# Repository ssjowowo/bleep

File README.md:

# Bleep

**A DIY touchscreen universal remote.** It's built around an ESP32-S3 on a main board of our own, with a 3.5″ IPS touch display, 14 physical keys, IR send and learn, haptics, and Home Assistant control over Wi-Fi. The case is 3D-printed and only 13 mm thick.

<p align="center">
  
  &nbsp;
  
</p>

## What it is

Most universal remotes either have a screen and few buttons, or lots of buttons and no screen. Bleep has both. The touchscreen shows activities, now-playing and smart-home controls. The keys you use without looking stay physical: a D-pad ring with OK, Back, Home, Mute, three app keys (YouTube, Netflix, Plex) and a volume rocker.

- **IR out**: two side-view 940 nm IR LEDs at the top end control TVs, receivers and boxes.
- **IR learning**: a 38 kHz receiver behind a small window under the screen copies codes from your old remotes.
- **Wi-Fi**: Home Assistant control of lights, scenes and media through the ESP32-S3.
- **Feel**: a coin vibration motor driven by a DRV2605L haptics driver.
- **Smart power**: lift-to-wake (accelerometer), wake on touch or any key, auto-brightness (light sensor), and a fuel gauge for an accurate battery percentage. Asleep it draws about 0.1–0.15 mA, so a charge lasts months.
- **USB-C** for charging and flashing.

The hardware is designed for all of this. The firmware's app and UI run today in an emulator (on the PC or in a browser) while the boards are being made; the ESP32-S3 port comes when they arrive. See [firmware/README.md](firmware/README.md).

The industrial design comes from a concept pack made in Claude Design (design **1b "Pebble"**, in `design/`). The brand (wordmark, logo lockup) comes from the Bleep brand book.

## Status

| Part | State |
|---|---|
| Main board v1 | **Ordered** from JLCPCB on 2026-10-08 (5 boards, 2 assembled). The design is locked: the files in `hardware/mainboard/` are the ones in production. |
| Enclosure | Ready to print. 15.0 mm thick since 2026-11-13: the cell lies on the flat, uniform 1.5 mm back plate, which drops in and slides home under ledges in the side walls; back edges rounded 3 mm. |
| Display | BuyDisplay ER-TFT035IPS-6 + capacitive touch, **ordered** 2026-10-09. Its cable fold gets checked on the real panel before assembly. |
| Battery | EEMB 524261, 1500 mAh (sold as 5.2 mm, measured 5.5–6.0 mm thick); `BATT` in `layout.py` is set for 6.0 mm. |
| Firmware | App and UI (C + LVGL 9) running in a PC/browser emulator with 53 scripted test scenarios; the ESP-IDF build runs on the first board (since 2026-11-02), with a Home Assistant client tested against a real Home Assistant. [firmware/](firmware/) |

## Hardware at a glance

| | |
|---|---|
| Size | 60.7 × 182.2 × 15.0 mm |
| MCU | ESP32-S3-WROOM-1-N8R2 (8 MB flash, 2 MB PSRAM), antenna at the right edge beside the D-pad |
| Display | 3.5″ IPS 320 × 480, ILI9488 on an 8-bit parallel bus (much faster than SPI), FT6236 capacitive touch |
| Keys | 14 tactile switches, each on its own wake-capable GPIO |
| IR | 2 × VSMB2948SL LEDs (≈ 125 mA peaks), IRM-H638T receiver for learning |
| Sensors | MMA8452Q accelerometer, LTR-303ALS light sensor, MAX17048 fuel gauge |
| Power | 1-cell Li-Po, TP4056 charger with load sharing, ME6211 3.3 V LDO |
| Board | 2 layers, 0.8 mm, 54 × 178 mm. JLCPCB assembles the top side; you solder the ESP32 module, battery and motor on the underside. |
| Case | PETG, two colours for the key labels (flush inlays), plus translucent blue PETG for the IR and sensor windows (two small separate prints); the board screwed to the front shell (4 × M2×4) and the back plate dropped in and slid home under side ledges and two top hooks, then held by 2 × M2×10, all into heat-set inserts |

The parts list, pin map, assembly steps, ordering guide (≈ €130 in total, delivered to Cyprus) and firmware notes are in **[hardware/README.md](hardware/README.md)**.

## How it's built

Everything mechanical comes from one file, [`hardware/layout.py`](hardware/layout.py). It holds the display and part sizes, the key layout, where each part sits, the z stack and the screw points, and it runs fit checks on all of them. Two generators read it:

- **Enclosure**: `layout.py` writes `enclosure/params.scad`, and [`enclosure/remote.scad`](hardware/enclosure/remote.scad) (OpenSCAD) builds the front shell, its two windows, back plate, key caps and label inlays as STLs, plus interference checks.
- **Main board**: [`mainboard/gen_mainboard.py`](hardware/mainboard/gen_mainboard.py) places the parts in KiCad 10 from the same numbers. [Freerouting](https://github.com/freerouting/freerouting) routes it, then the generator adds ground pours, runs DRC and exports Gerbers, BOM and CPL for JLCPCB.

The board and the case can't drift apart. Since the board was ordered, `layout.py` checks every value the board was built from against `mainboard/pcb_lock.json`. It refuses to run if a case change would move one of them.

## Repository layout

```
design/              concept pack (open the .dc.html files in a browser), brand assets, outline drawings
hardware/
  layout.py          the single source of truth for the mechanics
  build.sh           rebuilds everything from layout.py
  enclosure/         OpenSCAD source and the printable STLs (enclosure/stl/)
  mainboard/         KiCad board, generator, routing logs; fab/ = Gerbers, BOM, CPL (locked)
  viewer/            3D colour viewer (three.js) for trying colourways
  docs/              datasheets and renders
HANDOFF.md           current working state, for picking the project up on another machine
```

## Building

```bash
cd hardware
./build.sh enclosure   # STLs, renders and fit checks
./build.sh viewer      # meshes for the 3D viewer (viewer/index.html)
```

You need Python 3 (no extra packages) and OpenSCAD 2021.01 or newer, on the PATH or set with `OPENSCAD=`. The board rebuild (`./build.sh pcb`) also needs KiCad 10 and Freerouting, and it's disabled while v1 is locked.

To open the 3D viewer locally, run `python3 -m http.server -d hardware/viewer 8742` and go to <http://localhost:8742>.

## Roadmap

1. Boards and display arrive: check the display cable fold, solder the underside parts, print the case.
2. Firmware: LVGL UI (activities, now playing, Home Assistant), IR send and learning through the RMT peripheral, deep sleep with key, touch and lift wake.
3. Fixes found on the real hardware go into a v2 board.

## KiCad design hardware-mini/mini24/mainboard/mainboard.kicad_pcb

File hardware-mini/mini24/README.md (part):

# Bleep mini24 — hardware (2.4" panel)

A hand-built Bleep with a 2.4" 240 × 320 IPS touch panel: v1's design language (glass to the top end, 5/20 mm corners, IR window in the top wall, sensor window + power key in the row under the screen, ring D-pad + OK, round keys, app pills, split volume bar, USB-C at the bottom), a smaller shell, a replaceable 1500 mAh cell on a connector (under the keys, for the balance in the hand), a PDM microphone and a 32 kHz crystal. Built in small quantities: JLCPCB makes the board and places the top side (Economic PCBA); the underside parts (the ESP32 module, the battery connector with its protection FET and resistor, the motor's wires) are soldered by hand with an iron; the rest comes from LCSC, AliExpress and Ampul.

| | |
|---|---|
| Shell | **46.92 × 159.51 × 15.73 mm** |
| Display | BuyDisplay ER-TFT024IPS-3 (ST7789V, 4-wire SPI) + ER-TPC024-1 touch (FT6336U, I²C), one 50-pin FPC, 4.23 mm |
| ESP32 | ESP32-S3-WROOM-1-**N8R2** (PCB antenna), across the board on the underside, antenna at the right edge |
| Cell | **Ampul AM4289 "504050"**, 5.0 × 40 × 50 mm, 1500 mAh, PCM, on a Molex PicoBlade plug; **under the keys** (y 91.5–141.5), behind a printed deck |
| Main board | 40.12 × 154.8 mm (incl. the USB tab), 2 layers, 0.8 mm, **green mask, lead-free HASL** (what JLC's Economic PCBA allows at 0.8 mm); a 13.65 × 9.55 mm window under the panel FPC's touch section |
| Assembly | **JLCPCB Economic PCBA, top side only**; you solder the underside by iron: U1 (module), J2 (PicoBlade) with Q4 (SOT-23) and R28 (0603) beside it, the motor's wires, J3's four shell legs, and the module's EPAD through its three holes (§6) |

Everything comes from [`layout.py`](layout.py) (the mechanical source of truth: positions, stack, GPIO map, fit checks):

```bash
./build.sh            # fit checks, STLs + interference checks, board (place/route/DRC/fab), viewer meshes
./build.sh enclosure  # params.scad, STLs, interference + insertion-path checks
./build.sh pcb        # main board: place -> Freerouting -> SES -> pours/refs/BOM -> DRC -> fab outputs
./build.sh viewer     # ../viewer/mini24.json
```

Needs Python 3, OpenSCAD (`~/.local/bin/openscad`), and Docker with `../tools/kicad.sh` (KiCad 10) and `../tools/freerouting.sh` (Freerouting 2.5). Set `BLEEP_LOCK=/path/heavy.lock` to serialise the heavy steps with another build.

**Status (2026-10-13, cell moved under the keys, §14):** fit checks pass; OpenSCAD interference checks empty / zero volume, insertion-path checks empty; board fully routed, KiCad DRC (all severities) **0 violations / 0 unconnected**; Gerbers, drill, BOM, position file, assembly drawings and renders in `mainboard/fab/`. Not built yet. The mini28 audit's findings that apply here are built in (§9), and so are the mini24 audit's (§10) and the final audit's (§11).

---

## 1. The antenna problem and how it's solved

The WROOM-1's keep-out (no copper on either layer from 1.5 mm before the antenna section to the board edge, 3.5 mm past the module's long sides) is a 7.8 × 25 mm block at the right edge. On this 40 mm board v1's layout would have put the D-pad's RIGHT switch and the right-column power key inside it (that's why the concept failed v1's checks).

**Chosen:** keep the module across the board on the underside with its antenna 0.3 mm inside the right edge (the best spot for a PCB antenna short of overhanging the board), put it **directly below the folded display FPC**, and start the key cluster **below the keep-out**:

- The keep-out begins 0.3 mm below the fold's outer edge (y 67.66) and ends at y 92.96 (the board's rule area). The D-pad's RIGHT switch body (+1 mm) starts right after it. The UP switch and the power key sit over the module (on the top side), which is fine: only copper within the keep-out matters, and the module carries them.
- The **power key moves 4.5 mm in from the right column** (x 31.5 instead of 35.96), so its pads stay 0.7 mm clear of the keep-out. The row under the screen reads: sensor window (left column), mic hole (centre), power key (right of centre).
- Posts and screws are ≥ 4 mm from the keep-out (since §14 there is no screw on the right between the screen and the bottom boss; the nearest is H1, at the far left).
- Cost: about 1 mm of length over the concept (159.5 vs 158.2 mm; the last 0.3 is the IR LEDs' clearance to a panel slid up in its pocket), partly paid back by tightening the key rows (row pitch 23.0/11.5/10.0 instead of 23.5/12/10) and by a realistic, shorter FPC fold.

**Rejected:**
- Module lengthwise or at the bottom: the antenna end would sit in the 20 mm bottom corner, where the board is narrower than the keep-out; +20 mm of length.
- D-pad off-centre (2.3 mm left): breaks the design language.
- **WROOM-1U + U.FL FPC antenna** ([C3013944](https://www.lcsc.com/product-detail/C3013944.html) + Molex 146153-0050): there's no place for a 35 × 9 mm antenna that's away from the cell, the panel and the board's ground (the side walls are 1.6 mm from the board edge; under the key area it would sit 5 mm under a ground pour); 133 antennas in stock. Kept as the fallback.

Expect the antenna to be somewhat detuned by the hand and the PETG wall (1.6 mm away; Espressif asks for much more). Measure RSSI against v1 on the first build.

---

## 2. Stack (z from the back face, 5.0 mm cell)

| z (mm) | |
|---|---|
| 0 – 1.5 | back plate (flat, removable: 2 screws into the deck + 2 snap fingers) |
| 1.5 – 6.5 | **under the keys: the cell** (y 91.5–141.5) on the plate between its two side rails, +0.5 swell gap to 7.0. Under the screen and the module (open down to the plate): the module (3.1), the battery connector + plug (3.4) and Q4/R28 left of the module, the motor (3.3) under the screen, the plate's pillars and LCD fins, H1's head (1.6) |
| 7.0 – 7.6 | **the deck** (printed, 0.6 mm) under the key area, from y 90.26 down; the two bottom board screws' heads hang under it |
| 7.6 – 8.4 | main board, 0.8 mm (with a window under the touch section, see below) |
| 8.4 – 10.7 | under the LCD: **2.3 mm** — the panel FPC with the touch section, J1 (1.0), foam pads (1.5 + 1.0 mm soft foam, 8 % compressed) |
| 10.7 – 13.0 | LCD (2.3) |
| 13.0 – 14.93 | touch panel (PET on glass, 1.93) |
| 14.93 – 15.73 | front frame over the glass (0.8) |

Key area: front wall inner face z 14.13, switch actuators z 9.90, stems 3.53 mm with 0.1 mm designed play. The cell's thickness and the deck drive H (15.13 + the 0.6 mm deck): a 6 mm cell (604050, 1600 mAh, or 603450) would make it 16.73 mm, over the 16 mm limit (`layout.py` reports it).

**The touch section and the 2.3 mm gap (mini24 audit M1).** The panel's 50-pin FPC carries the touch panel's own tail soldered onto its contact face: the FT6336U and its parts on a 9 × 11 mm, 0.2 mm steel stiffener, rigid, up to 1.7 mm tall incl. the FPC. Along the FPC (DS 3.3 front and side views, the ER-TPC024-1 drawing, the listing photo) it sits at **s ≈ 12.5–21.5 mm** from the BL edge; its tall part ends at s ≈ 17–19. **Across**, it is placed by the ER-TPC024-1 drawing's own dimensions (final audit M1), measured from the lens's left edge (shell x 2.1): the CTP tail's 6-pad solder strip starts **9.61** in and is **4.00** wide (x 11.71–15.71, thin), and the **11.00 × 9.00** steel-stiffened controller box lies right of it: **x 15.71–26.71**, with the FT6336U at ≈ x 18.6–23.9 (scaled, the only undimensioned part). DS 3.3's front view agrees within 0.2 mm. That leaves only ≈ 0.5 mm of flexible FPC before the main tail's own stiffener (s 22–27), which must lie flat in J1 at the board. After the fold, the parts face the board.
- A taller bottom-contact ZIF (the audit's option a) doesn't solve it: its contact slot stays at the board (only its lid grows, per the PH15/PH20 drawings), so the FPC still has to come down to ≈ 0.3 mm above the board. J1 stays the 1.0 mm FH34SRJ.
- Instead the gap under the LCD grows from 2.0 to **2.3 mm** (shell +0.3 mm) and the board gets a **window** (**x 14.40–28.05, y 48.90–58.45**, 13.65 × 9.55 mm, 0.5 mm corner radii) under the controller box: the box ± 0.8 mm, plus ± 0.5 mm for the tail's lateral position, and its tall part's s range ± 1 mm. No copper within 0.45 mm of the cut. The section lies **tilted ≈ 10°**: its J1 end just above J1's slot (the 0.5 mm flex only bends gently, no S; its thin steel end may rest on the board's solder mask), its fold end just under the LCD's back, its tall part dipping into the window — at most to the board's underside, never below it (since §14 only open space and the back plate are behind it). The window stops 3.3 mm short of J1 so the display signals still have a way round to J1's pads. The window's coordinates are written as numbers in `layout.py`, not derived from the section, and `check()` tests them against the drawing-derived box (+0.8 +0.5 each side) and the tall part's s range (±1), so the check can't pass by construction; `remote.scad`'s FPC model places the strip and the box from the same drawing constants, and `fpc_vs_parts` sees them.
- **If the parts face the other way** (up), the section lies flat at J1's height with its parts in the 2.3 mm gap, 0.3 mm under the LCD: that also passes the checks, so the design doesn't depend on the facing.
- The 1:1 mock-up with the real panel (§6 step 0) settles s, the facing and the heights **before the boards are ordered**.

---

## 3. The cell, and why

**Ampul AM4289 "504050": 5.0 × 40 × 50 mm, 1500 mAh, 5.55 Wh, protection circuit fitted, bare leads** (€8.13, "in stock at supplier"; [ampul.eu](https://ampul.eu/en/battery/4395-li-pol-battery-1500mah-37v-504050)).

- DESIGN.md's first choice. **Where it sits (since 2026-10-13, §14): under the keys**, on the back plate right below the module (the module can't go under the panel: the LCD's metal frame would detune its antenna). The bay runs from 0.6 mm below the module's pocket (y 90.66) to y 142.36: **51.70 mm stop to stop, 41.22 mm between the plate's two side rails** (0.8 mm wide, rising beside the cell in the board-to-wall gap, down to the bottom stops' line; 0.61 mm clear per side of a 40 mm cell). Small chamfered stops (2 mm wide, 1.5 mm tall) hold its ends: at the top (lead) end 8 mm either side of the centre, away from the corners where the leads leave, under the module; at the bottom end 3.5 mm either side of the centre.
- **The bay takes cells up to 40.0 × 50.5 mm** including the PCM (0.6 mm to spare per side and at each end; `layout.py` prints the same). Margins of the nominal cell (y 91.51–141.51): **2.05 mm to the module's outline** (1.45 to its pocket), for a centred cell **0.69 mm** from its bottom corners to where the plate's lip would be; the lip is cut away beside the bottom corners, so even a cell pushed into a corner (against a rail and a stop) keeps **0.81 mm to the wall** and touches only the rail and the stop; **1.5 mm** to the deck's bosses, **7.0 mm** to the bottom board screws' heads, **8.5 mm** to the zone kept for the USB-C's underside joints. ≤ 5.0 mm thick.
- **The deck** (§14) lies 0.5 mm over the cell (its swell gap) and carries the keys, so a key press doesn't land on the cell.
- Compared: 603560 (6 × 35 × 60, 1500 mAh) is 1 mm thicker for the same capacity and 10 mm longer: it doesn't fit under the keys; 604050 (1600 mAh) is +7 % for +1 mm: the shell would be 16.73 mm, over the 16 mm limit now that the deck is in the stack. Fallback 603450 (1200 mAh, 6 mm) likewise doesn't fit the limit any more.
- Charge current 500 mA (PROG 2.4 k, 0.33 C).
- Runtime ≈ 3.3 weeks at 15 min/day (scaled from v1's estimate; unverified).

**The plug sits at the cell's top end** (the user's choice, 2026-10-13; DESIGN.md's first brief said "at the bottom"): J2 lies on the underside in the free corner left of the module (x 6.0–14.6, y 79.7–85.7), its mouth facing **down** towards the cell, 5.8 mm above the cell's top end, so the mated plug (3.5 mm past the mouth) points at the cell and the leads come straight up into it; spare lead length can loop in the 3 mm under the module. The leads are bare: cut them to the real path from the cell's lead corner to J2's mouth + 10 mm (≈ 30 mm from the near corner, up to ≈ 40 mm if the leads leave the far corner), and crimp a PicoBlade housing on (§6, step 6). **J2's pin 1 is + (silk "+" on the underside).** A P-MOSFET (Q4) in the + lead protects the board if the plug is crimped the wrong way round (§5).

---

## 4. Main board

`mainboard/gen_mainboard.py` (adapted from v1's): `place` → `dsn` → Freerouting → `ses` → `tidy` → `finish` → `fab`; `mainboard/route.sh` runs them, `../fab.sh` exports. KiCad 10 DRC with `--severity-all` (errors and warnings, silk included): **0 violations, 0 unconnected, 0 footprint errors** (`mainboard/drc.rpt`), also with a zone refill.

Rules (JLCPCB standard 2-layer): 0.13 mm clearance, 0.15 mm tracks, 0.6/0.3 vias, 0.4 mm copper to edge. Power: VBAT/VSYS/BAT_RAW **0.6 mm** (router and the hand-drawn VSYS rail), 3V3 and other power nets 0.3 mm. **No vias in SMD pads**, with one deliberate exception: three 0.6/0.3 GND thermal vias (tented from below) down the middle of the TP4056's exposed pad, with its paste as two strips beside them (≈ 50 %), into the bottom pour under it. `fab` fails the build if any other via's hole comes within 0.15 mm of an SMD pad (`via_at_smd off` for the router; the GND helpers skip pads). GND is a pour on both layers; `fab` stitches cut-off pour pieces, gives any GND pad the pour can't reach its own via, and stitches the two pours on a ≈ 4 mm grid wherever there's room plus a row at 1.2 mm pitch just outside the antenna keep-out's edges (mini24 audit M6). Finish: lead-free HASL, green mask (in the board file and the order; Economic PCBA at 0.8 mm offers nothing else).

Routing notes (for the audit):
- **GND is not routed by Freerouting.** With the bottom pour exported as a plane, Freerouting 2.5 fans out a via at every GND pin and its rip-up passes then collapse on this board (24 → 120+ unrouted, never recovering). `dsn()` removes the plane and the GND pins from the routing (GND's fixed copper stays as obstacles); every signal then routes in one or two passes, and `fab()` handles GND.
- Hand-drawn copper (fixed for the router): the module fan-out (a bottom stub from every used pin to a via just past the module's edge, as v1's), the 3V3 run from the LDO up under the RIGHT key to the module's pin 2, the EN and 3V3 drops, the LDO's pin wiring (v1's), the crystal's ~2.5 mm drops from pins 8/9, the **VSYS rail** (load-sharing pair → LDO, and up the left edge → IR LED resistors → down the right edge → the backlight anode stub at J1 pin 1), the USB D+/D− crossover (v1's), GND vias for the DRV2605L, J1's pins 6/9/43/49, and U4, C8, C9, C12, C17 (where the left edge's traffic cuts up the bottom pour), the mic's L/R tie, the TP4056's EP vias, and **the mic's whole fan-out**: the four inner pads can't all leave on one layer in the order their destinations need (CLK upper-left → IO36's via to the north-west, DATA lower-left → IO44's via to the north-east, VDD lower-right → R27 → 3V3 from the south), and the module's underside is out of bounds, so DATA runs under the mic and up its right side **between R27's two pads** (R27 is in series in the supply: 3V3 outside, MIC_VDD inside, with C22 next to the mic), CLK goes straight up to its via with R30 beside it.
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
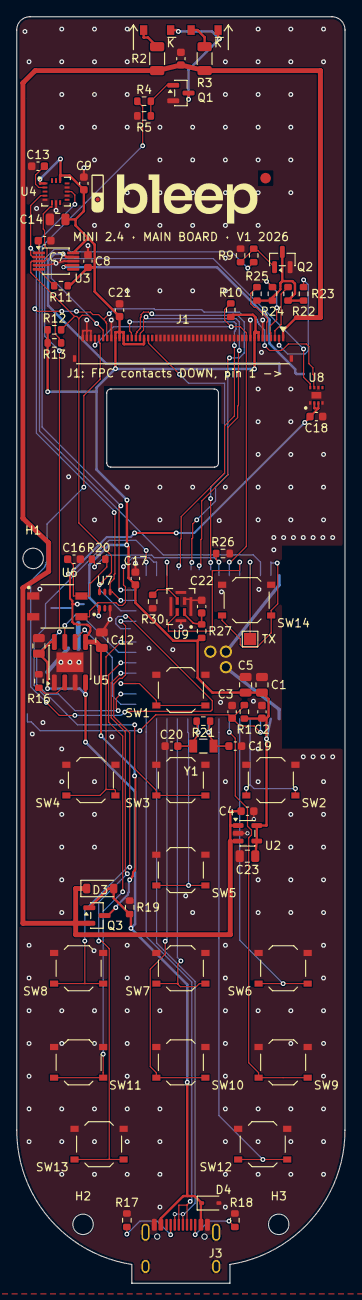
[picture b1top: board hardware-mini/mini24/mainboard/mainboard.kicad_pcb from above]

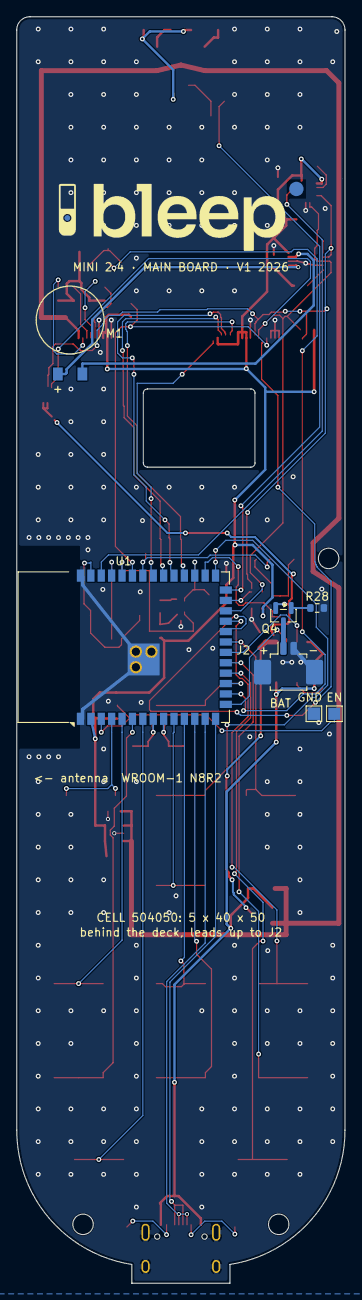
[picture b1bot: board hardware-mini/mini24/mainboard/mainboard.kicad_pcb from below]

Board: 2 copper layers, 40.1 x 154.8 mm, 92 parts (9 on the bottom side), 64 nets.

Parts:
C1: 22uF; C_0805_2012Metric
C2, C9, C13, C22: 100nF; C_0603_1608Metric
C3, C4, C7, C8, C17, C18, C21: 1uF; C_0603_1608Metric
C5, C11, C12, C14, C23: 10uF; C_0805_2012Metric
C6, C16: 10uF; C_0603_1608Metric
C19, C20: 8.2pF C0G; C_0603_1608Metric
D1, D2: VSMB2948SL; VSMB2948SL_SideView
D3: B5819W; D_SOD-123
D4: LESD3Z5.0T1G; D_SOD-323
H1, H2, H3: M2; MountingHole_2.5mm
J1: FH34SRJ-50S-0.5SH(50); Hirose_FH34SRJ-50S-0.5SH
J2: 53261-0271; Molex_PicoBlade_53261-0271_1x02-1MP_P1.25mm_Horizontal
J3: TYPE-C 16PIN 2MD(073); USB_C_Receptacle_HRO_TYPE-C-31-M-12
LOGO_BACK1, LOGO_BACK2: logo LED dot
LOGO_FRONT1, LOGO_FRONT2: logo LED dot
M1: ERM 0827 (8 mm coin, wired); Motor_8mm_WirePads
Q1, Q2: AO3400A; SOT-23
Q3, Q4: AO3401A; SOT-23
R1, R10, R19, R28: 10k; R_0603_1608Metric
R2, R3: 22R; R_1206_3216Metric
R4, R8, R27: 100R; R_0603_1608Metric
R5, R9, R11, R26, R30: 100k; R_0603_1608Metric
R12, R13: 4.7k; R_0603_1608Metric
R16: 2.4k; R_0603_1608Metric
R17, R18: 5.1k; R_0603_1608Metric
R20: 220R; R_0603_1608Metric
R21: 10M DNP; R_0603_1608Metric
R22, R23, R24, R25: 68R; R_0603_1608Metric
SW1, SW2, SW3, SW4, SW5, SW6, SW7, SW8, SW9, SW10, SW11, SW12, SW13, SW14: TS-1187A-B-A-B; SW_Push_1P1T_XKB_TS-1187A
TP1, TP2, TP3: test pad; TestPoint_Pad_1.5x1.5mm
U1: ESP32-S3-WROOM-1-N8R2; ESP32-S3-WROOM-1
U2: ME6211C33M5G-N; SOT-23-5
U3: DRV2605LDGST; MSOP-10_3x3mm_P0.5mm
U4: MMA8452QR1; MMA8452Q_QFN-16_3x3mm_P0.5mm
U5: TP4056; SOIC-8-1EP_3.9x4.9mm_P1.27mm_EP2.41x3.3mm
U6: IRM-H638T/TR2; IRM-H638T
U7: LTR-303ALS-01
U8: MAX17048G+T10; MAX17048_TDFN-8_2x2mm
U9: MSM261DHT006; MSM261DHT006_LGA-8_3x4mm
Y1: 32.768kHz 6pF; Epson_FC-135_3.2x1.5mm

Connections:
3V3: C1.1, C2.1, C5.1, C8.1, C9.1, C14.2, C17.1, C21.1, C23.2, J1.7, J1.8, J1.35, J1.40, J1.41, J1.42, R1.1, R10.1, R11.2, R12.1, R13.1, R27.1, U1.2, U2.4, U2.5, U3.10, U4.1, U4.14, U7.1
ACC_BYP: C13.2, U4.2
ACC_INT: U1.38, U4.11
BAT_G: Q4.1, R28.1
BAT_RAW: J2.1, Q4.3
BL_G: Q2.1, R8.2, R9.1
BL_K: Q2.3, R22.1, R23.1, R24.1, R25.1
BL_K1: J1.2, R22.2
BL_K2: J1.3, R23.2
BL_K3: J1.4, R24.2
BL_K4: J1.5, R25.2
BL_PWM: R8.1, U1.16
CC1: J3.A5, R17.1
CC2: J3.B5, R18.1
CHRG: U1.20, U5.7
DBG_TX: TP3.1, U1.37
DISP_RST: J1.10, J1.47, R10.2, U1.35
DRV_EN: R11.1, U3.5
DRV_REG: C7.1, U3.1
EN: C3.1, R1.2, TP1.1, U1.3
GND: C1.2, C2.2, C3.2, C4.2, C5.2, C6.2, C7.2, C8.2, C9.2, C11.2, C12.2, C13.1, C14.1, C16.2, C17.2, C18.2, C19.2, C20.1, C21.2, C22.2, C23.1, D4.2, J1.6, J1.9, J1.11, J1.12, J1.13, J1.14, J1.15, J1.16, J1.17, J1.18, J1.19, J1.20, J1.21, J1.22, J1.23, J1.24, J1.25, J1.26, J1.27, J1.28, J1.29, J1.30, J1.31, J1.32, J1.43, J1.48, J1.49, J1.50, J1.MP, J2.2, J2.MP, J3.A1, J3.A12, J3.B1, J3.B12, J3.SH, Q1.2, Q2.2, R5.1, R9.2, R16.2, R17.2, R18.2, R19.2, R26.2, R28.2, R30.2, SW1.1, SW2.1, SW3.1, SW4.1, SW5.1, SW6.1, SW7.1, SW8.1, SW9.1, SW10.1, SW11.1, SW12.1, SW13.1, SW14.1, TP2.1, U1.1, U1.40, U1.41, U2.2, U3.4, U3.8, U4.5, U4.7, U4.10, U4.12, U5.1, U5.3, U5.9, U6.1, U6.2, U7.3, U8.1, U8.4, U8.6, U8.9, U9.2, U9.5, U9.6, U9.7, U9.8
IRRX_PWR: R20.1, R26.1, U1.34
IRRX_V: C16.1, R20.2, U6.4
IR_G: Q1.1, R4.2, R5.2
IR_RX: U1.28, U6.3
IR_TX: R4.1, U1.26
K_BACK: SW6.2, U1.5
K_DOWN: SW5.2, U1.10
K_HOME: SW7.2, U1.11
K_LEFT: SW4.2, U1.21
K_MUTE: SW8.2, U1.23
K_NFLX: SW10.2, U1.12
K_OK: SW3.2, U1.27
K_PLEX: SW9.2, U1.6
K_PWR: SW14.2, U1.39
K_RIGHT: SW2.2, U1.4
K_UP: SW1.2, U1.17
K_VOLDN: SW13.2, U1.18
K_VOLUP: SW12.2, U1.7
K_YT: SW11.2, U1.19
LCD_CS: J1.38, U1.30
LCD_DC: J1.36, U1.32
LCD_MOSI: J1.34, U1.33
LCD_SCK: J1.37, U1.31
LED1_A: D1.2, R2.2
LED2_A: D2.2, R3.2
LED_K: D1.1, D2.1, Q1.3
MIC_CLK: R30.1, U1.29, U9.3
MIC_DATA: U1.36, U9.4
MIC_VDD: C22.1, R27.2, U9.1
MOT_N: M1.2, U3.9
MOT_P: M1.1, U3.7
PROG: R16.1, U5.2
SCL: J1.44, R13.2, U1.25, U3.2, U4.4, U7.4, U8.7
SDA: J1.45, R12.2, U1.24, U3.3, U4.6, U7.6, U8.8
STDBY: U1.15, U5.6
TP_INT: J1.46, U1.22
USB_DN: J3.A7, J3.B7, U1.13
USB_DP: J3.A6, J3.B6, U1.14
VBAT: C12.1, C18.1, Q3.3, Q4.2, U5.5, U8.2, U8.3
VBUS: C11.1, D3.2, D4.1, J3.A4, J3.A9, J3.B4, J3.B9, Q3.1, R19.1, U5.4, U5.8
VSYS: C4.1, C6.1, D3.1, J1.1, Q3.2, R2.1, R3.1, U2.1, U2.3
XTAL_N: C20.2, R21.1, U1.9, Y1.1
XTAL_P: C19.1, R21.2, U1.8, Y1.2

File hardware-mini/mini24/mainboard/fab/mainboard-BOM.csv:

Ref,Value,Footprint,LCSC / source,Qty,Side,Note,Link
C1,22uF,C_0805_2012Metric,C45783,1,top,,https://www.lcsc.com/product-detail/C45783.html
C2 C9 C13 C22,100nF,C_0603_1608Metric,C14663,4,top,"X7R 50 V (YAGEO CC0603KRX7R9BB104, JLC basic)",https://www.lcsc.com/product-detail/C14663.html
C3 C4 C7 C8 C17 C18 C21,1uF,C_0603_1608Metric,C15849,7,top,"X5R 50 V (Samsung CL10A105KB8NNNC, JLC basic)",https://www.lcsc.com/product-detail/C15849.html
C5 C11 C12 C14 C23,10uF,C_0805_2012Metric,C15850,5,top,"X5R 25 V 0805 (Samsung CL21A106KAYNNNE, JLC basic)",https://www.lcsc.com/product-detail/C15850.html
C6 C16,10uF,C_0603_1608Metric,C19702,2,top,10 V X5R 0603,https://www.lcsc.com/product-detail/C19702.html
C19 C20,8.2pF C0G,C_0603_1608Metric,C1685,2,top,32 kHz load caps (6.8 pF C1679 to tune),https://www.lcsc.com/product-detail/C1685.html https://www.lcsc.com/product-detail/C1679.html
D1 D2,VSMB2948SL,VSMB2948SL_SideView,C6604342,2,top,940 nm side-view IR LED,https://www.lcsc.com/product-detail/C6604342.html
D3,B5819W,D_SOD-123,C64885,1,top,Schottky 1 A 40 V (MDD; JSCJ C8598 is low on stock),https://www.lcsc.com/product-detail/C64885.html https://www.lcsc.com/product-detail/C8598.html
D4,LESD3Z5.0T1G,D_SOD-323,C383210,1,top,"5 V TVS on VBUS, cathode (band) = VBUS",https://www.lcsc.com/product-detail/C383210.html
J1,FH34SRJ-50S-0.5SH(50),Hirose_FH34SRJ-50S-0.5SH,C3169104,1,top,"50-pin 0.5 mm FPC ZIF, 1.0 mm, top+bottom contact, back flip",https://www.lcsc.com/product-detail/C3169104.html
J2,53261-0271,Molex_PicoBlade_53261-0271_1x02-1MP_P1.25mm_Horizontal,C177225,1,bottom,"PicoBlade 2-pin right angle, battery",https://www.lcsc.com/product-detail/C177225.html
J3,TYPE-C 16PIN 2MD(073),USB_C_Receptacle_HRO_TYPE-C-31-M-12,C2765186,1,top,USB-C receptacle 16-pin,https://www.lcsc.com/product-detail/C2765186.html
M1,"ERM 0827 (8 mm coin, wired)",Motor_8mm_WirePads,AliExpress: 1005007600971536 (variant 8x2.7mm),1,bottom,"vibration motor, stuck to the underside",https://www.aliexpress.com/item/1005007600971536.html
Q1 Q2,AO3400A,SOT-23,C20917,2,top,N-MOSFET,https://www.lcsc.com/product-detail/C20917.html
Q3,AO3401A,SOT-23,C15127,1,top,P-MOSFET,https://www.lcsc.com/product-detail/C15127.html
Q4,AO3401A,SOT-23,C15127,1,bottom,P-MOSFET,https://www.lcsc.com/product-detail/C15127.html
R1 R10 R19,10k,R_0603_1608Metric,C25804,3,top,"1 % (UNI-ROYAL 0603WAF1002T5E, JLC basic)",https://www.lcsc.com/product-detail/C25804.html
R2 R3,22R,R_1206_3216Metric,C17958,2,top,"IR LED series, 1206 / 250 mW (burst power)",https://www.lcsc.com/product-detail/C17958.html
R4 R8 R27,100R,R_0603_1608Metric,C22775,3,top,,https://www.lcsc.com/product-detail/C22775.html
R5 R9 R11 R26 R30,100k,R_0603_1608Metric,C25803,5,top,,https://www.lcsc.com/product-detail/C25803.html
R12 R13,4.7k,R_0603_1608Metric,C23162,2,top,,https://www.lcsc.com/product-detail/C23162.html
R16,2.4k,R_0603_1608Metric,C22940,1,top,TP4056 PROG: 500 mA,https://www.lcsc.com/product-detail/C22940.html
R17 R18,5.1k,R_0603_1608Metric,C23186,2,top,,https://www.lcsc.com/product-detail/C23186.html
R20,220R,R_0603_1608Metric,C22962,1,top,,https://www.lcsc.com/product-detail/C22962.html
R21,10M (DO NOT FIT),R_0603_1608Metric,C114606,1,top,32 kHz bias: leave EMPTY (fit only if the crystal won't start),https://www.lcsc.com/product-detail/C114606.html
R22 R23 R24 R25,68R,R_0603_1608Metric,C27592,4,top,"backlight, one per LED cathode",https://www.lcsc.com/product-detail/C27592.html
R28,10k,R_0603_1608Metric,C98220,1,bottom,"underside, by iron (LCSC loose stock)",https://www.lcsc.com/product-detail/C98220.html
SW1 SW2 SW3 SW4 SW5 SW6 SW7 SW8 SW9 SW10 SW11 SW12 SW13 SW14,TS-1187A-B-A-B,SW_Push_1P1T_XKB_TS-1187A,C318884,14,top,tact switch 5.1x5.1x1.5,https://www.lcsc.com/product-detail/C318884.html
U1,ESP32-S3-WROOM-1-N8R2,ESP32-S3-WROOM-1,C2913204,1,bottom,"Wi-Fi/BLE module, 8 MB flash, 2 MB quad PSRAM (NOT N8R8)",https://www.lcsc.com/product-detail/C2913204.html
U2,ME6211C33M5G-N,SOT-23-5,C82942,1,top,3.3 V 500 mA LDO,https://www.lcsc.com/product-detail/C82942.html
U3,DRV2605LDGST,MSOP-10_3x3mm_P0.5mm,C425927,1,top,"haptic driver, VSSOP-10",https://www.lcsc.com/product-detail/C425927.html
U4,MMA8452QR1,MMA8452Q_QFN-16_3x3mm_P0.5mm,C11360,1,top,accelerometer QFN-16 (hot air),https://www.lcsc.com/product-detail/C11360.html
U5,TP4056,SOIC-8-1EP_3.9x4.9mm_P1.27mm_EP2.41x3.3mm,C16581,1,top,"Li-ion charger, ESOP-8 (EP needs paste + reflow)",https://www.lcsc.com/product-detail/C16581.html
U6,IRM-H638T/TR2,IRM-H638T,C91447,1,top,38 kHz IR receiver (learning),https://www.lcsc.com/product-detail/C91447.html
U7,LTR-303ALS-01,LTR-303ALS-01,C364577,1,top,ambient light sensor DFN-6 (hot air),https://www.lcsc.com/product-detail/C364577.html
U8,MAX17048G+T10,MAX17048_TDFN-8_2x2mm,C2682616,1,top,fuel gauge TDFN-8 + EP (hotplate),https://www.lcsc.com/product-detail/C2682616.html
U9,MSM261DHT006,MSM261DHT006_LGA-8_3x4mm,C51928215,1,top,"PDM MEMS mic, TOP port Ø0.65; no washing, don't cover the port",https://www.lcsc.com/product-detail/C51928215.html
Y1,32.768kHz 6pF,Epson_FC-135_3.2x1.5mm,C20340322,1,top,Epson FC-135 32.7680KA-E,https://www.lcsc.com/product-detail/C20340322.html
—,display ER-TFT024IPS-3 + ER-TPC024-1 (capacitive),50-pin 0.5 mm FPC,"AliExpress: 1005008088847517 (BuyDisplay, CTP variant)",1,,not on the board,https://www.aliexpress.com/item/1005008088847517.html
—,"Li-Po 504050 5.0x40x50 1500 mAh, PCM",bare leads,Ampul: AM4289 https://ampul.eu/en/battery/4395-li-pol-battery-1500mah-37v-504050,1,,not on the board,https://ampul.eu/en/battery/4395-li-pol-battery-1500mah-37v-504050
—,PicoBlade housing 51021-0200,for the cell's leads,C293613,1,,not on the board,https://www.lcsc.com/product-detail/C293613.html
—,PicoBlade crimp 50079-8100 (26-28 AWG) or 50058-8000 (28-32 AWG),by the cell's lead gauge,C587850 / C293573,2,,not on the board,https://www.lcsc.com/product-detail/C587850.html https://www.lcsc.com/product-detail/C293573.html
—,M2 x 3 x 3.2 heat-set insert,"front-shell post + 2 bosses, 2 in the deck's bosses",C51938879,5,,not on the board,https://www.lcsc.com/product-detail/C51938879.html
—,M2 x 4 pan head,"3 board screws (2 also clamp the deck), with the washer below; 2 back-plate screws into the deck, heads flush in the plate's counterbores",C357393,5,,not on the board,https://www.lcsc.com/product-detail/C357393.html
—,"M2 flat washer DIN 125 A / ISO 7089, Ø5 x 0.3, A2",under each board-screw head (the holes are 2.5 mm),"AliExpress: 32812536491 (pick M2, 304 stainless, 100 pcs); EU alternative: 3DJake https://www.3djake.com/cnc-kitchen/standard-washer-din-125-s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",3,,not on the board,https://www.aliexpress.com/item/32812536491.html https://www.3djake.com/cnc-kitchen/standard-washer-din-125-s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
—,"SOFT double-sided foam tape (PE/EVA sponge), 1.0 mm and 1.5 mm",panel pads: one 1.5 + one 1.0 layer per pad (8 % into the 2.3 gap); 1.0 mm also for the mic gasket ring (OD 2.3 / ID 1.1),"AliExpress: 1005003980172009 (pick 1.0 mm and 1.5 mm, 10 mm wide; fallback 4000803370856: stack 1.0 + 0.5) or any SOFT foam tape of those thicknesses",1,,not on the board,https://www.aliexpress.com/item/1005003980172009.html https://www.aliexpress.com/item/4000803370856.html
—,Kapton tape 10-20 mm,"tack strips for the folded panel, over the cell's PCM end",C92418 (10 mm x 33 m roll; 20 mm: C92419),1,,not on the board,https://www.lcsc.com/product-detail/C92418.html https://www.lcsc.com/product-detail/C92419.html

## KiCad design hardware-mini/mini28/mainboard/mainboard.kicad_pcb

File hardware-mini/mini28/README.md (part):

# Bleep mini28 — hardware (2.8" panel)

The 2.8" Bleep: v1's "Pebble" shell and key layout around a 2.8" IPS panel with glass touch, one main board of our own, a replaceable 1500 mAh cell under the keys (in the lower half, so the remote isn't top-heavy) that plugs in at its top end (reverse-polarity protected), a PDM microphone for push-to-talk, and a 32.768 kHz crystal. Built in small quantities: **JLCPCB places the top side** (Economic PCBA, top only) and **you solder the underside by hand** (the ESP32 module, the battery header, its reverse-polarity FET and resistor, the motor wires).

| | |
|---|---|
| Shell | **54.4 × 168.8 × 15.3 mm** (concept print: 54.4 × 167.8 × 14.5; 14.1 with the cell under the screen until 2026-10-13, §12) |
| Main board | 49.6 × 165.1 mm (incl. the USB-C tab), 0.8 mm, 2 layers, **green mask, lead-free HASL** (the only finish JLC's Economic PCBA offers at 0.8 mm). KiCad DRC: **0 violations, 0 unconnected** (`--severity-all`, with JLCPCB's silk minimums as rules) |
| Display | EastRising ER-TFT028A2-4 (ILI9341, IPS, 240 × 320, **4-wire SPI**) + ER-TPC028-4.1 glass CTP (FT6206). 50-pin FPC into J1, separate 6-pin touch tail into J2 |
| ESP32 | ESP32-S3-WROOM-1-**N8R2** on the underside, antenna at the right edge (seen from the front) |
| Battery | **Ampul AM7240 "484251": 4.8 × 42 × 51 mm, 1500 mAh**, protected, **under the keys** (below the module) on a printed deck, plugs into a PicoBlade header (J4) on the underside at its top end |
| New vs v1 | SPI panel, separate touch ZIF, PDM mic (MSM261DHT006) under a port hole, 32 kHz crystal, battery connector + reverse-polarity FET, USB ESD/TVS, TX debug pad, top side assembled by JLC (Economic), underside by hand |

Changes after the independent audit (`../audit/mini28_electrical.md`, `../audit/mini28_mechanical.md`) are listed in §9.

Everything is generated from [`layout.py`](layout.py) (mechanics, positions, GPIO map, fit checks):

```bash
./build.sh layout      # enclosure/params.scad + fit checks
./build.sh enclosure   # STLs in enclosure/stl/ + interference checks
./build.sh viewer      # ../viewer/mini28.json (+ the mini28 entry of ../viewer/dims.json)
./build.sh pcb         # place -> DSN -> Freerouting -> SES -> pours/stitching/BOM -> DRC (mainboard/drc.rpt)
./build.sh fab         # assembly values, DRC, Gerbers + drill (zip), position file, assembly drawings, renders
(cd mainboard && ../../tools/kicad.sh python3 gen_mainboard.py retrofit && ../../tools/kicad.sh python3 gen_mainboard.py bom)
                       # part data (values, C-numbers, footprint graphics), stackup and BOM onto the routed board, no re-route
BLEEP_BATT="42.3,51.4,4.9" ./build.sh enclosure    # a measured cell: the back plate's rails and stops follow it
```

KiCad 10 and Freerouting 2.5 run in Docker through `../tools/kicad.sh` and `../tools/freerouting.sh`. Heavy steps take a shared lock (`HEAVY_LOCK`, default `$TMPDIR/bleep-heavy.lock`). OpenSCAD: `OPENSCAD=` or `~/.local/bin/openscad`. `./build.sh pcb` retries the routing until DRC is clean (§8 risk 10); a re-route changes the copper, so for part changes that keep the pads use `retrofit` instead.

## 1. Mechanics

### Stack (z from the outer back face)

| z (mm) | |
|---|---|
| 0 – 1.5 | back plate (flat, held by 2 snap fingers at the top + 2 × M2×8 at the bottom, heads ≈ 1.4 mm below the back face in 3.0 mm counterbores) |
| 1.5 – 6.3 | the 4.8 mm cell (under the keys, y 104.9–155.9); the module, motor, PicoBlade header + plug, Q4/R24 elsewhere |
| 6.3 – 6.8 | swell gap over the cell |
| 6.8 – 7.6 | **the deck** (printed, 0.8 mm) under the board in the key area, from just below the module to the bottom edge; the board screws' washers and heads hang under it (to z 4.9), beside the cell |
| 7.6 – 8.4 | main board, 0.8 mm |
| 8.4 – 10.2 | under the LCD (**1.8 mm**): J1/J2 (FH34SRJ, 1.0 mm), both FPC runs, the touch tail's controller section (≤ 1.5 mm, chip down) with the main FPC (0.15) on it, foam pads; parts there ≤ 1.45 mm |
| 10.2 – 13.0 | LCD + backlight (2.8) |
| 13.0 – 14.5 | CTP glass (1.5) |
| 14.5 – 15.3 | front frame over the glass (0.8) |

H = 10.5 + cell thickness (9.7 + the 0.8 mm deck). Under the screen the board's underside carries only the motor and a few pillars now; the plate is 6.1 mm below the board there.

### Panel and the two FPC folds (from the drawings in `../docs/mini28/`)

- The module (LCD + white frame, 50.20 × 69.30) is wider than the glass (49.50 × 69.20, tops flush), so the glass pocket is sized on the module. The panel's top edge starts 0.53 mm past the IR LEDs' backs.
- **Display FPC**: 50 pins, 26.70 mm long, contacts on the FRONT face → after folding back under the LCD they face the board (bottom contact). Pin 1 stays on the right. Its parts strip (≤ 1.0 mm, rigid) is 3.7–5.6 mm out, on the back face.
- **Touch tail**: 6 pins, 37.90 mm long, centre 19.25 mm left of the panel centre, contacts on the BACK face → after the fold they face **up** (top contact). It runs outside the main FPC in the bend and lowest under the LCD. Its rigid FT6206 section (12 mm wide, 7.8–16.9 mm along the tail, ≤ 1.5 mm) ends up under the panel's bottom-left corner, chip down: the board keeps that area free of parts, and it sets the 1.8 mm gap.
- **Fold model** (redone after the audit): the radii follow the real landing heights. The tail lands on its own 1.5 mm controller section (bend r 1.65); the main FPC lands on the tail there (r 1.18). Both run 1.0 mm straight out of the panel first, so the main FPC's parts strip ends inside its bend and the tail's controller section starts after its bend, flat under the panel (fit-checked). J1 sits at (27.20, 57.49), J2 at (7.95, 47.78), each **2.0 mm** closer to the fold than the model needs (`FPC_SLACK`). The slack errs long on purpose: a short FPC is fatal (only a new board fixes it), a long one just bulges the fold (≈ 2.8 mm of room before the row under the screen). 2.0 mm covers the main FPC's rigid parts strip (3.7–5.6 mm out) being forced into a chord across the bend instead of the modelled arc (≈ 1.2 mm more FPC, ≈ 1.5 mm for the touch tail that wraps it) plus the drawings' ±0.5 mm length tolerance (fit-checked, as is the bulge of a long FPC). **Do the fold mock-up before ordering the boards if you can (§4 step 7).**
- **Hirose FH34SRJ** (both connectors): 1.0 mm high, contacts top **and** bottom, 0.3 mm FPC (both tails are 0.30 ± 0.03), back-flip lid. Contact 1 is at the footprint's +x end and the FPC enters from +y (from the fold), so **FPC pin n lands on pad n** for both (v1's XUNPU was 51 − n). Lands 0.3 × 0.8 as Hirose recommends; **stencil apertures 0.25 × 0.65** (Hirose's metal mask) to keep the 0.5 mm pitch free of bridges.

### Board support, cell and screws

- The board clears the walls by **0.6 mm** all round (PETG shrinks 0.2–0.5 % over 165 mm; set the slicer's XY shrink compensation for PETG anyway). Its side and top edges lie over the back plate's locating lip, and under the screen the **rails stand on the lip's footprint** (x 2.15–3.25 from each wall), carrying 0.85 mm of board edge; four Ø3 **pillars** carry the board's middle there (x 27.2 y 22 / 48, (40, 66), (20, 76)), now that no cell lies under the screen. The screws locate the board; the rails and pillars only stop it bowing.
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
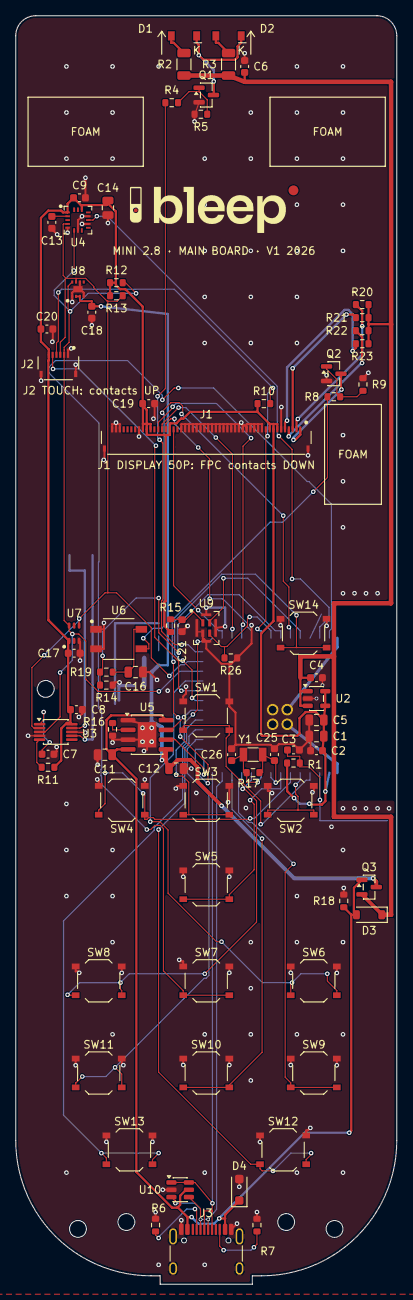
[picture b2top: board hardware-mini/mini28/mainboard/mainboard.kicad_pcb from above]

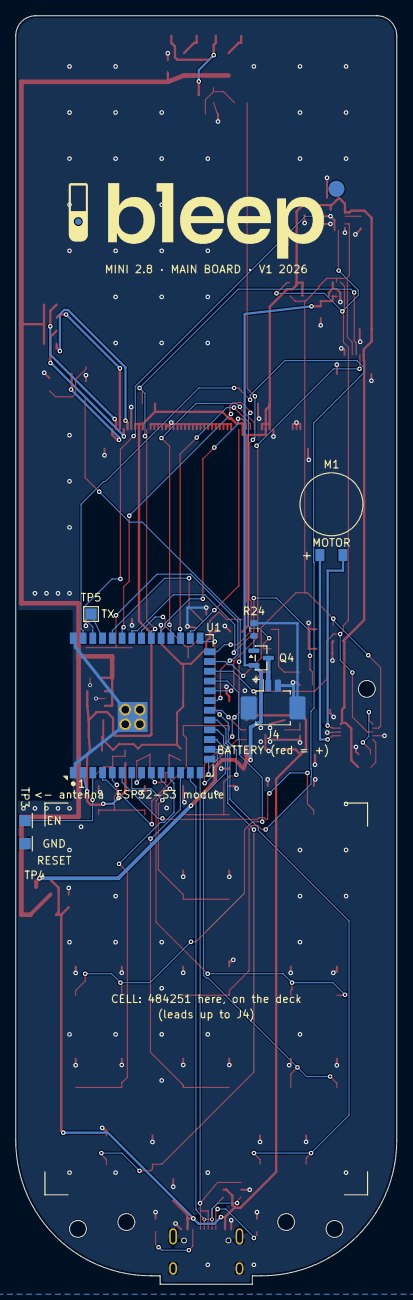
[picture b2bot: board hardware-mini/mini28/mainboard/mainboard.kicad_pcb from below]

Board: 2 copper layers, 49.6 x 165.1 mm, 96 parts (10 on the bottom side), 64 nets.

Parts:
C1: 22uF; C_0805_2012Metric
C2, C9, C13, C20, C21: 100nF X7R 50V; C_0603_1608Metric
C3, C4, C7, C8, C17, C18, C19: 1uF X5R 50V; C_0603_1608Metric
C5, C11, C12, C14, C16: 10uF X5R 25V; C_0805_2012Metric
C6: 10uF; C_0603_1608Metric
C25, C26: 8.2pF C0G; C_0603_1608Metric
D1, D2: VSMB2948SL; VSMB2948SL_SideView
D3: B5819W; D_SOD-123
D4: SMF5.0A; D_SOD-123F
H1, H2, H3, H4, H5: M2; MountingHole_2.2mm_M2
J1: FH34SRJ-50S-0.5SH(50); Hirose_FH34SRJ-50S-0.5SH
J2: FH34SRJ-6S-0.5SH(50); Hirose_FH34SRJ-6S-0.5SH
J3: TYPE-C 16PIN 2MD(073); USB_C_Receptacle_HRO_TYPE-C-31-M-12
J4: PicoBlade 53261-0271; Molex_PicoBlade_53261-0271_1x02-1MP_P1.25mm_Horizontal
LOGO_BACK1, LOGO_BACK2: logo LED dot
LOGO_FRONT1, LOGO_FRONT2: logo LED dot
M1: 8 mm coin motor (wired); LRA_8mm_WirePads
Q1, Q2: AO3400A; SOT-23
Q3, Q4: AO3401A; SOT-23
R1, R10, R18, R24: 10k; R_0603_1608Metric
R2, R3: 22R 1206; R_1206_3216Metric
R4, R8, R15: 100R; R_0603_1608Metric
R5, R9, R11, R14, R26: 100k; R_0603_1608Metric
R6, R7: 5.1k; R_0603_1608Metric
R12, R13: 4.7k; R_0603_1608Metric
R16: 2.4k (PROG 500 mA); R_0603_1608Metric
R17: 10M DNP; R_0603_1608Metric
R19: 220R; R_0603_1608Metric
R20, R21, R22, R23: 56R; R_0603_1608Metric
SW1, SW2, SW3, SW4, SW5, SW6, SW7, SW8, SW9, SW10, SW11, SW12, SW13, SW14: TS-1187A-B-A-B; SW_Push_1P1T_XKB_TS-1187A
TP3, TP4, TP5: pad; TestPoint_Pad_1.5x1.5mm
U1: ESP32-S3-WROOM-1-N8R2; ESP32-S3-WROOM-1
U2: ME6211C33M5G-N; SOT-23-5
U3: DRV2605LDGST; MSOP-10_3x3mm_P0.5mm
U4: MMA8452QR1; MMA8452Q_QFN-16_3x3mm_P0.5mm
U5: TP4056-42-ESOP8; SOIC-8-1EP_3.9x4.9mm_P1.27mm_EP2.41x3.3mm
U6: IRM-H638T/TR2; IRM-H638T
U7: LTR-303ALS-01
U8: MAX17048G+T10; MAX17048_TDFN-8_2x2mm
U9: MSM261DHT006; MSM261DHT006_LGA-8_3x4mm
U10: USBLC6-2SC6; SOT-23-6
Y1: FC-135 32.768kHz 6pF; Crystal_SMD_3215-2Pin_3.2x1.5mm

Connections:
3V3: C1.2, C2.2, C5.2, C8.1, C9.1, C14.2, C17.1, C19.1, C20.1, J1.7, J1.8, J1.9, J1.35, J1.40, J1.41, J1.42, J2.6, R1.1, R10.1, R11.2, R12.1, R13.1, R15.1, U1.2, U2.4, U2.5, U3.10, U4.1, U4.14, U7.1
ACC_BYP: C13.2, U4.2
ACC_INT: U1.38, U4.11
BAT_G: Q4.1, R24.1
BAT_RAW: J4.1, Q4.3
BL_A1: J1.2, R20.1
BL_A2: J1.3, R21.1
BL_A3: J1.4, R22.1
BL_A4: J1.5, R23.1
BL_G: Q2.1, R8.2, R9.1
BL_K: J1.1, Q2.3
BL_PWM: R8.1, U1.16
CC1: J3.A5, R6.1
CC2: J3.B5, R7.1
CHRG: U1.20, U5.7
DBG_TX: TP5.1, U1.37
DISP_RST: J1.10, J2.4, R10.2, U1.32
DRV_EN: R11.1, U3.5
DRV_REG: C7.1, U3.1
EN: C3.1, R1.2, TP3.1, U1.3
GND: C1.1, C2.1, C3.2, C4.2, C5.1, C6.2, C7.2, C8.2, C9.2, C11.2, C12.2, C13.1, C14.1, C16.2, C17.2, C18.1, C19.2, C20.2, C21.1, C25.2, C26.2, D4.2, J1.6, J1.11, J1.12, J1.13, J1.14, J1.15, J1.16, J1.17, J1.18, J1.19, J1.20, J1.21, J1.22, J1.23, J1.24, J1.25, J1.26, J1.27, J1.28, J1.29, J1.30, J1.31, J1.32, J1.43, J1.48, J1.49, J1.50, J1.MP, J2.1, J2.MP, J3.A1, J3.A12, J3.B1, J3.B12, J3.SH, J4.2, J4.MP, Q1.2, Q2.2, R5.1, R6.2, R7.2, R9.2, R14.2, R16.1, R18.2, R24.2, R26.2, SW1.1, SW2.1, SW3.1, SW4.1, SW5.1, SW6.1, SW7.1, SW8.1, SW9.1, SW10.1, SW11.1, SW12.1, SW13.1, SW14.1, TP4.1, U1.1, U1.40, U1.41, U2.2, U3.4, U3.8, U4.5, U4.7, U4.10, U4.12, U5.1, U5.3, U5.9, U6.1, U6.2, U7.3, U8.1, U8.4, U8.6, U8.9, U9.2, U9.5, U9.6, U9.7, U9.8, U10.2
IRRX_PWR: R14.1, R19.1, U1.34
IRRX_V: C16.1, R19.2, U6.4
IR_G: Q1.1, R4.2, R5.2
IR_RX: U1.35, U6.3
IR_TX: R4.1, U1.26
K_BACK: SW6.2, U1.23
K_DOWN: SW5.2, U1.7
K_HOME: SW7.2, U1.39
K_LEFT: SW4.2, U1.6
K_MUTE: SW8.2, U1.10
K_NFLX: SW10.2, U1.12
K_OK: SW3.2, U1.27
K_PLEX: SW9.2, U1.11
K_PWR: SW14.2, U1.21
K_RIGHT: SW2.2, U1.5
K_UP: SW1.2, U1.4
K_VOLDN: SW13.2, U1.19
K_VOLUP: SW12.2, U1.18
K_YT: SW11.2, U1.17
LCD_CS: J1.38, U1.30
LCD_DC: J1.36, U1.31
LCD_MOSI: J1.34, U1.28
LCD_SCK: J1.37, U1.29
LED1_A: D1.2, R2.2
LED2_A: D2.2, R3.2
LED_K: D1.1, D2.1, Q1.3
MIC_CLK: R26.1, U1.33, U9.3
MIC_DATA: U1.36, U9.4
MIC_VDD: C21.2, R15.2, U9.1
MOT_N: M1.2, U3.9
MOT_P: M1.1, U3.7
PROG: R16.2, U5.2
SCL: J2.3, R13.2, U1.25, U3.2, U4.4, U7.4, U8.7
SDA: J2.2, R12.2, U1.24, U3.3, U4.6, U7.6, U8.8
STDBY: U1.15, U5.6
TP_INT: J2.5, U1.22
USB_DN: J3.A7, J3.B7, U1.13, U10.3, U10.4
USB_DP: J3.A6, J3.B6, U1.14, U10.1, U10.6
VBAT: C12.1, C18.2, Q3.3, Q4.2, U5.5, U8.2, U8.3
VBUS: C11.1, D3.2, D4.1, J3.A4, J3.A9, J3.B4, J3.B9, Q3.1, R18.1, U5.4, U5.8, U10.5
VSYS: C4.1, C6.1, D3.1, Q3.2, R2.1, R3.1, R20.2, R21.2, R22.2, R23.2, U2.1, U2.3
XTAL_N: C26.1, R17.1, U1.9, Y1.2
XTAL_P: C25.1, R17.2, U1.8, Y1.1

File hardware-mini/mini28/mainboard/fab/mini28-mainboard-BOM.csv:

References,Value,Footprint,Source (JLC/LCSC C-number or AliExpress item),Qty per board,Side,Who / how,Link
C1,22uF,C_0805_2012Metric,C45783,1,top,"top, JLC",https://www.lcsc.com/product-detail/C45783.html
C2 C9 C13 C20 C21,100nF X7R 50V,C_0603_1608Metric,C14663,5,top,"top, JLC",https://www.lcsc.com/product-detail/C14663.html
C3 C4 C7 C8 C17 C18 C19,1uF X5R 50V,C_0603_1608Metric,C15849,7,top,"top, JLC",https://www.lcsc.com/product-detail/C15849.html
C5 C11 C12 C14 C16,10uF X5R 25V,C_0805_2012Metric,C15850,5,top,"top, JLC",https://www.lcsc.com/product-detail/C15850.html
C6,10uF,C_0603_1608Metric,C19702,1,top,"top, JLC",https://www.lcsc.com/product-detail/C19702.html
C25 C26,8.2pF C0G,C_0603_1608Metric,C1685,2,top,"top, JLC",https://www.lcsc.com/product-detail/C1685.html
D1 D2,VSMB2948SL,VSMB2948SL_SideView,C6604342,2,top,"top, JLC (lens to the top edge)",https://www.lcsc.com/product-detail/C6604342.html
D3,B5819W,D_SOD-123,C64885,1,top,"top, JLC (cathode bar = silk line)",https://www.lcsc.com/product-detail/C64885.html
D4,SMF5.0A,D_SOD-123F,C19077497,1,top,"top, JLC (cathode bar = silk line, to VBUS)",https://www.lcsc.com/product-detail/C19077497.html
J1,FH34SRJ-50S-0.5SH(50),Hirose_FH34SRJ-50S-0.5SH,C3169104,1,top,"top, JLC",https://www.lcsc.com/product-detail/C3169104.html
J2,FH34SRJ-6S-0.5SH(50),Hirose_FH34SRJ-6S-0.5SH,C224194,1,top,"top, JLC",https://www.lcsc.com/product-detail/C224194.html
J3,TYPE-C 16PIN 2MD(073),USB_C_Receptacle_HRO_TYPE-C-31-M-12,C2765186,1,top,"top, JLC; shell legs (plated slots): JLC hand-solders them per the order remark, or iron them yourself",https://www.lcsc.com/product-detail/C2765186.html
J4,PicoBlade 53261-0271,Molex_PicoBlade_53261-0271_1x02-1MP_P1.25mm_Horizontal,C177225,1,bottom,"underside, iron",https://www.lcsc.com/product-detail/C177225.html
M1,8 mm coin motor (wired),LRA_8mm_WirePads,AliExpress: 1005007600971536 (8x2.7mm),1,bottom,"underside: stick on, solder its wires",https://www.aliexpress.com/item/1005007600971536.html
Q1 Q2,AO3400A,SOT-23,C20917,2,top,"top, JLC",https://www.lcsc.com/product-detail/C20917.html
Q3,AO3401A,SOT-23,C15127,1,top,"top, JLC",https://www.lcsc.com/product-detail/C15127.html
Q4,AO3401A,SOT-23,C15127,1,bottom,"underside, iron (next to J4)",https://www.lcsc.com/product-detail/C15127.html
R1 R10 R18,10k,R_0603_1608Metric,C25804,3,top,"top, JLC",https://www.lcsc.com/product-detail/C25804.html
R2 R3,22R 1206,R_1206_3216Metric,C17958,2,top,"top, JLC (IR bursts: 0.18 W avg, 0.54 W peak)",https://www.lcsc.com/product-detail/C17958.html
R4 R8 R15,100R,R_0603_1608Metric,C22775,3,top,"top, JLC",https://www.lcsc.com/product-detail/C22775.html
R5 R9 R11 R14 R26,100k,R_0603_1608Metric,C25803,5,top,"top, JLC",https://www.lcsc.com/product-detail/C25803.html
R6 R7,5.1k,R_0603_1608Metric,C23186,2,top,"top, JLC",https://www.lcsc.com/product-detail/C23186.html
R12 R13,4.7k,R_0603_1608Metric,C23162,2,top,"top, JLC",https://www.lcsc.com/product-detail/C23162.html
R16,2.4k (PROG 500 mA),R_0603_1608Metric,C22940,1,top,"top, JLC",https://www.lcsc.com/product-detail/C22940.html
R17,10M DNP,R_0603_1608Metric,C114606,1,top,"top, DO NOT FIT (footprint only)",https://www.lcsc.com/product-detail/C114606.html
R19,220R,R_0603_1608Metric,C22962,1,top,"top, JLC",https://www.lcsc.com/product-detail/C22962.html
R20 R21 R22 R23,56R,R_0603_1608Metric,C25196,4,top,"top, JLC",https://www.lcsc.com/product-detail/C25196.html
R24,10k,R_0603_1608Metric,C98220,1,bottom,"underside, iron (next to J4)",https://www.lcsc.com/product-detail/C98220.html
SW1 SW2 SW3 SW4 SW5 SW6 SW7 SW8 SW9 SW10 SW11 SW12 SW13 SW14,TS-1187A-B-A-B,SW_Push_1P1T_XKB_TS-1187A,C318884,14,top,"top, JLC",https://www.lcsc.com/product-detail/C318884.html
U1,ESP32-S3-WROOM-1-N8R2,ESP32-S3-WROOM-1,C2913204,1,bottom,"underside, iron + EPAD through the 4 holes",https://www.lcsc.com/product-detail/C2913204.html
U2,ME6211C33M5G-N,SOT-23-5,C82942,1,top,"top, JLC",https://www.lcsc.com/product-detail/C82942.html
U3,DRV2605LDGST,MSOP-10_3x3mm_P0.5mm,C425927,1,top,"top, JLC",https://www.lcsc.com/product-detail/C425927.html
U4,MMA8452QR1,MMA8452Q_QFN-16_3x3mm_P0.5mm,C11360,1,top,"top, JLC (QFN)",https://www.lcsc.com/product-detail/C11360.html
U5,TP4056-42-ESOP8,SOIC-8-1EP_3.9x4.9mm_P1.27mm_EP2.41x3.3mm,C16581,1,top,"top, JLC (EP needs paste)",https://www.lcsc.com/product-detail/C16581.html
U6,IRM-H638T/TR2,IRM-H638T,C91447,1,top,"top, JLC",https://www.lcsc.com/product-detail/C91447.html
U7,LTR-303ALS-01,LTR-303ALS-01,C364577,1,top,"top, JLC (DFN)",https://www.lcsc.com/product-detail/C364577.html
U8,MAX17048G+T10,MAX17048_TDFN-8_2x2mm,C2682616,1,top,"top, JLC (DFN + EP)",https://www.lcsc.com/product-detail/C2682616.html
U9,MSM261DHT006,MSM261DHT006_LGA-8_3x4mm,C51928215,1,top,"top, JLC (no washing, don't cover the port)",https://www.lcsc.com/product-detail/C51928215.html
U10,USBLC6-2SC6,SOT-23-6,C7519,1,top,"top, JLC (pin-1 dot)",https://www.lcsc.com/product-detail/C7519.html
Y1,FC-135 32.768kHz 6pF,Crystal_SMD_3215-2Pin_3.2x1.5mm,C20340322,1,top,"top, JLC",https://www.lcsc.com/product-detail/C20340322.html
(display),"ER-TFT028A2-4 IPS 2.8"" (ILI9341) + ER-TPC028-4.1 CTP (FT6206)",-,buydisplay.com: ER-TFT028A2-4 with the ER-TPC028-4.1 CTP option (AliExpress 1005005309636436 only as a fallback: its photos show the ER-TFTM028-4 module; confirm with the seller),1,-,"plugs into J1 + J2; buy first, fold mock-up before ordering boards",https://www.aliexpress.com/item/1005005309636436.html
(battery),"Ampul AM7240 Li-Pol 484251 4.8x42x51 mm 1500 mAh, protected",-,ampul.eu: 4060-li-pol-battery-1500mah-37v-484251,1,-,bare leads: crimp the plug below,https://ampul.eu/en/battery/4060-li-pol-battery-1500mah-37v-484251
(battery plug),Molex PicoBlade 51021-0200 housing,-,C293613,1,-,,https://www.lcsc.com/product-detail/C293613.html
(battery plug),Molex PicoBlade crimp 50079-8100 (26-28 AWG) or 50058-8000 (28-32 AWG),-,C587850 / C293573,2,-,pick by the measured lead gauge,https://www.lcsc.com/product-detail/C587850.html https://www.lcsc.com/product-detail/C293573.html
(mic gasket),foam ring OD 2.2 / ID 1.4 punched from 1 mm double-sided foam tape,-,"AliExpress: 1005007483857645 (10 mm, as v1)",1,-,also the panel's foam pads,https://www.aliexpress.com/item/1005007483857645.html
(screws),M2 x 4 pan head (board + deck -> posts),-,C357393,3,-,with a washer under each head,https://www.lcsc.com/product-detail/C357393.html
(washers),"M2 flat washer DIN 125 A / ISO 7089, Ø5 x 0.3, A2",-,"AliExpress: 32812536491 (pick M2, 304 stainless, 100 pcs); EU alternative: 3DJake https://www.3djake.com/cnc-kitchen/standard-washer-din-125-s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",3,-,"under the 3 board-screw heads, on the deck (its holes are 2.4 mm)",https://www.aliexpress.com/item/32812536491.html https://www.3djake.com/cnc-kitchen/standard-washer-din-125-s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
(screws),M2 x 8 pan head (back plate),-,"AliExpress: 1005005581270091 (M2, 8 mm)",2,-,,https://www.aliexpress.com/item/1005005581270091.html
(inserts),"M2 x 3 x 3.2 knurled brass heat-set insert (M2 thread, L 3.0, OD 3.2)",-,"C51938879 (LCSC: XHHD SZTB1063 double-knurled heat-set insert; AliExpress backup 1005008666672949, pick M2x3x3.2)",5,-,holes in the shell are 3.0 x 4.0 deep for OD 3.2,https://www.lcsc.com/product-detail/C51938879.html https://www.aliexpress.com/item/1005008666672949.html
(tape),"Kapton tape 10-20 mm (cell pull tab, screw heads next to the cell)",-,C92418 (10 mm x 33 m roll; 20 mm: C92419),1,-,,https://www.lcsc.com/product-detail/C92418.html https://www.lcsc.com/product-detail/C92419.html
